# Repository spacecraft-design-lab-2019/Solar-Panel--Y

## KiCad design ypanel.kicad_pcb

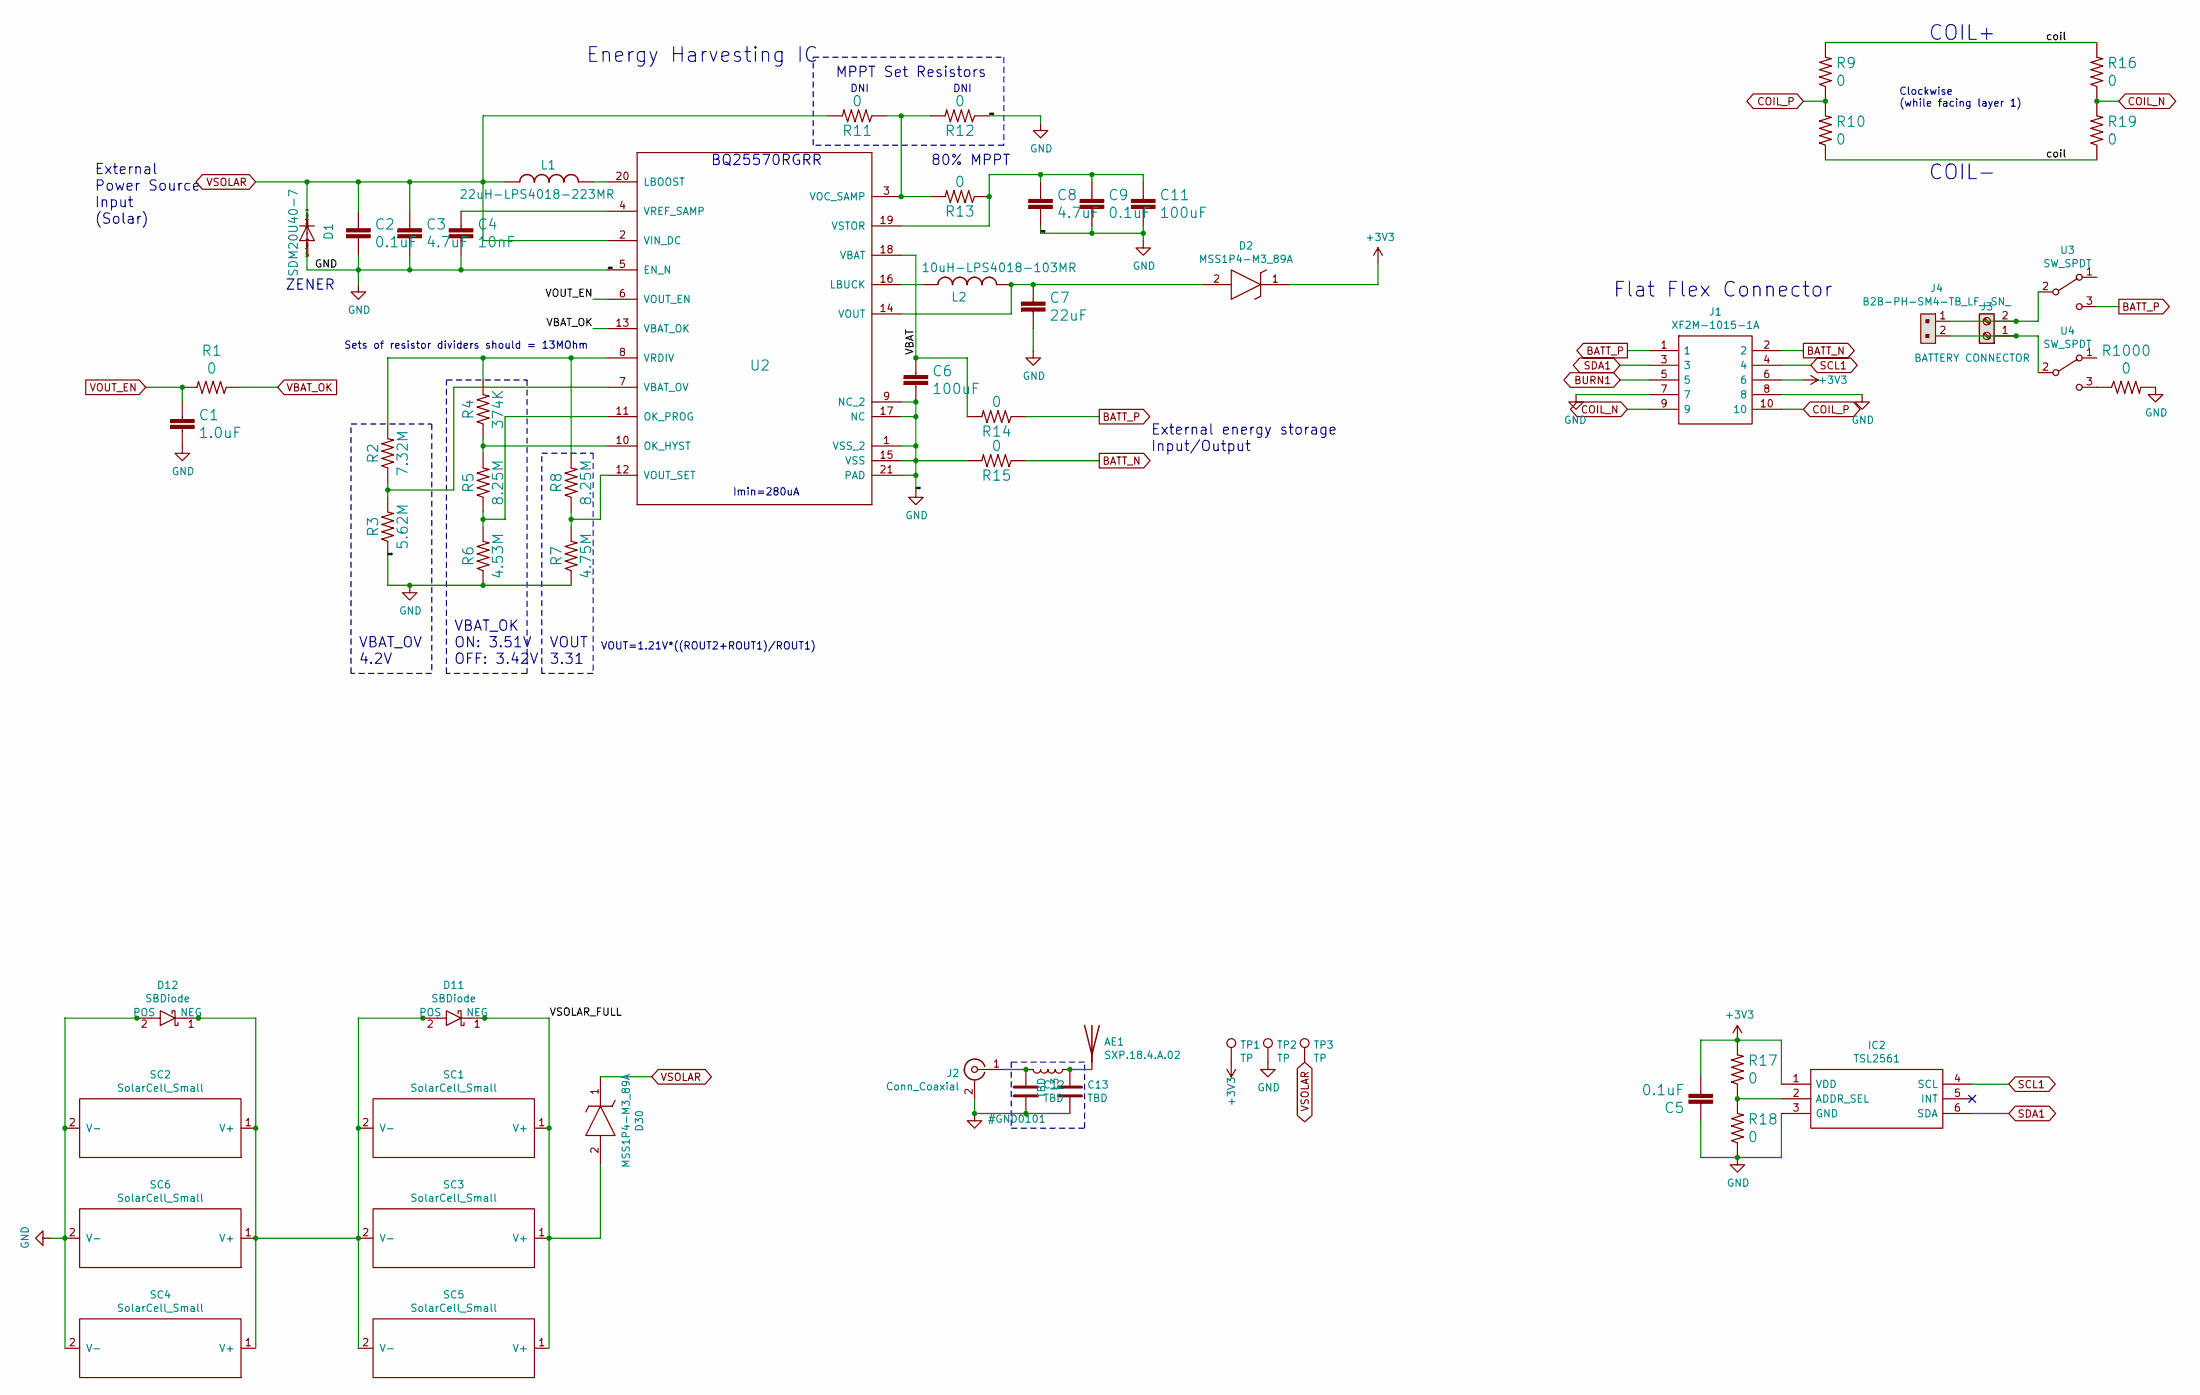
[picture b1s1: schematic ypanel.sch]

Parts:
AE1: SXP.18.4.A.02
C1: 1.0uF; C_0402_1005Metric
C2, C5, C9: 0.1uF; C_0402_1005Metric
C3, C8: 4.7uF; C_0402_1005Metric
C4: 10nF; C_0402_1005Metric
C6, C11: 100uF; C_0603_1608Metric
C7: 22uF; C_0402_1005Metric
C12, C13: TBD; C_0201_0603Metric
D1: SDM20U40-7; SOD523
D2, D30: MSS1P4-M3_89A; MICROSMP; Manufacturer_Part_Number MSS1P4-M3/89A; Mouser Part Number 625-MSS1P4-M3
D11, D12: SBDiode; SB Diode
IC2: TSL2561; Manufacturer_Part_Number TSL2561; Mouser Part Number N/A
J1: XF2M-1015-1A; Manufacturer_Part_Number XF2M-1015-1A; Mouser Part Number 653-XF2M-1015-1A
J2: Conn_Coaxial; U.FL_Hirose_U.FL-R-SMT-1_Vertical
J3: BATTERY CONNECTOR; SCREWTERMINAL-3.5MM-2_LOCK
J4: B2B-PH-SM4-TB_LF__SN_; JST_PH_B2B-PH-SM4-TB_1x02-1MP_P2.00mm_Vertical; MPN B2B-PH-SM4-TB(LF)(SN); Digi-Key_PN 455-1734-1-ND
L1: 22uH-LPS4018-223MR; LPS4018
L2: 10uH-LPS4018-103MR; LPS4018
L3: TBD; L_0201_0603Metric
R1, R9, R10, R11, R12, R13, R14, R15, R16, R17, R18, R19, R1000: 0; R_0402_1005Metric
R2: 7.32M; R_0402_1005Metric
R3: 5.62M; R_0402_1005Metric
R4: 374K; R_0402_1005Metric
R5, R8: 8.25M; R_0402_1005Metric
R6: 4.53M; R_0402_1005Metric
R7: 4.75M; R_0402_1005Metric
SC1, SC2, SC3, SC4, SC5, SC6: SolarCell_Small; KXOB25-05X3F
TP1, TP2, TP3: TP; TestPoint_THTPad_D1.0mm_Drill0.5mm
U2: Value; QFN50P350X350X100-21N-D
U3: SW_SPDT; D2F-L2-2
U4: SW_SPDT; D2F-L2

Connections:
+3V3: C5.2, D2.1, IC2.1 (VDD), J1.6, R17.2, TP1.1
/VBAT: C6.1, R14.2, U2.18 (VBAT)
/VSOLAR_FULL: D11.1 (NEG), D30.2, SC1.1 (V+), SC3.1 (V+), SC5.1 (V+)
/coil: R9.2, R10.1, R16.2, R19.1
BATT_N: J1.2, R15.1
BATT_P: J1.1, R14.1, U3.3 (C)
BURN1: J1.5
COIL_N: J1.9, R16.1, R19.2
COIL_P: J1.10, R9.1, R10.2
unnamed: AE1.1, C12.1, C13.1, J2.1 (In), L3.1, L3.2
unnamed: C4.1, U2.4 (VREF_SAMP)
unnamed: C7.1, D2.2, L2.2, U2.14 (VOUT)
unnamed: C8.1, C9.1, C11.1, R13.1, U2.19 (VSTOR)
unnamed: D11.2 (POS), D12.1 (NEG), SC1.2 (V-), SC2.1 (V+), SC3.2 (V-), SC4.1 (V+), SC5.2 (V-), SC6.1 (V+)
unnamed: IC2.2 (ADDR_SEL), R17.1, R18.2
unnamed: J3.1, J4.2, U4.2 (B)
unnamed: J3.2, J4.1, U3.2 (B)
unnamed: L1.2, U2.20 (LBOOST)
unnamed: L2.1, U2.16 (LBUCK)
unnamed: R2.1, R3.2, U2.7 (VBAT_OV)
unnamed: R2.2, R4.2, R8.2, U2.8 (VRDIV)
unnamed: R4.1, R5.2, U2.10 (OK_HYST)
unnamed: R5.1, R6.2, U2.11 (OK_PROG)
unnamed: R7.2, R8.1, U2.12 (VOUT_SET)
unnamed: R11.1, R12.2, R13.2, U2.3 (VOC_SAMP)
unnamed: R1000.1, U4.3 (C)
SCL1: IC2.4 (SCL), J1.4
SDA1: IC2.6 (SDA), J1.3
VBAT_OK: R1.1, U2.13 (VBAT_OK)
VOUT_EN: C1.1, R1.2, U2.6 (VOUT_EN)
VSOLAR: C2.1, C3.1, D1.C, D30.1, L1.1, R11.2, TP3.1, U2.2 (VIN_DC)

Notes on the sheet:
Flat Flex Connector
DNI
ZENER
VOUT 3.31
80% MPPT
VBAT_OK ON: 3.51V OFF: 3.42V
Imin=280uA
External Power Source Input (Solar)
External energy storage Input/Output
BQ25570RGRR
Energy Harvesting IC
VBAT_OV 4.2V
Sets of resistor dividers should = 13MOhm
VOUT=1.21V*((ROUT2+ROUT1)/ROUT1)
MPPT Set Resistors
COIL+
COIL-
Clockwise (while facing layer 1)

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
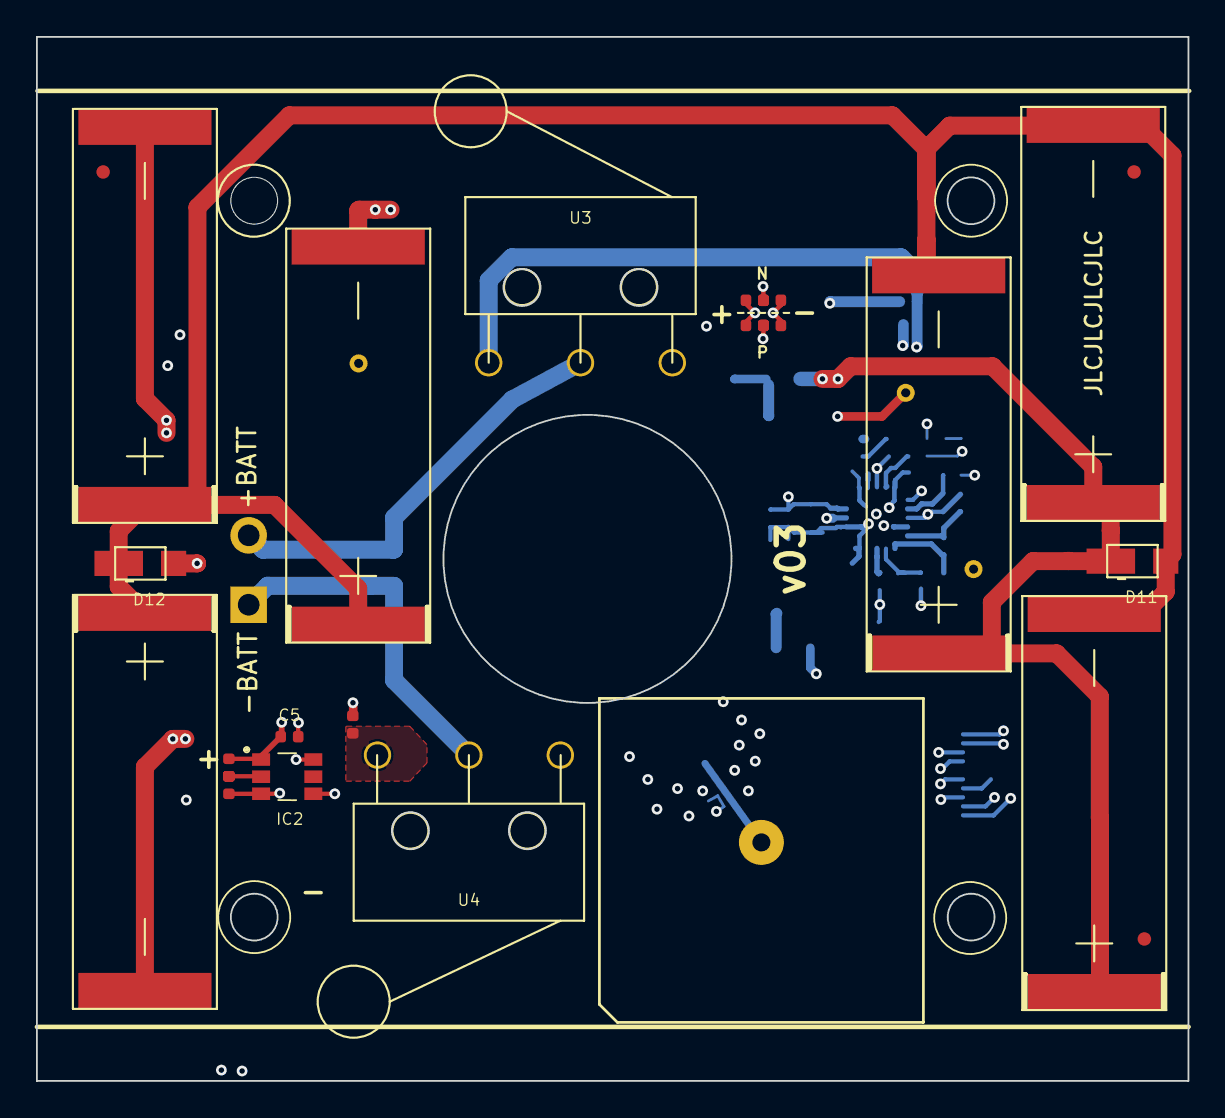
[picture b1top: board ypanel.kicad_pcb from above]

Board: 6 copper layers, 64.0 x 58.0 mm, 55 parts (0 on the bottom side), 31 nets.

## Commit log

2019-10-21 Added -Y PCB files (still in progress)
2019-10-23 Updated -Y PCB design
2019-10-24 Incorporated patch antenna and switches
2019-10-24 Added flatflex and phototransistor to -Y
2019-10-25 Added finished version 1 of -Y PCB
2019-10-25 starting on -Y board
2019-10-25 killer coils
2019-10-26 -Y board finished
2019-10-26 zipped fabrication files for all but +Y
2019-10-26 JLCPCB fab output
2019-10-26 adding interactive BOMs for +/-X,-Y,+-Z
2019-10-27 +Y panel read for fab
2019-10-27 JLCPCB output files
2019-10-29 Added step file of -Y panel
2019-10-30 Updated step file with additional 3D part models
2019-10-31 Added killswitches to step file
2019-11-01 stencil outputs
2019-11-14 Changed board outline to account for structures requirements
2019-12-03 Updated -Y PCB Layout
2019-12-03 Modified -Y Layout
2019-12-20 v01 order + repo overhaul
2020-02-12 repaired schematic so it matches PCB
2020-02-12 Updated -Y
    moved killswitches & flat-flex connector to new locations
2020-02-13 Added step file of -Y
2020-02-15 Added new antenna to -Y
2020-02-20 updated 3d footprint paths and generated new step file
2020-02-23 fixed antenna footprint and regenerated step file
2020-02-26 moved camera hole and other components
2020-02-28 Changed magnetorquer coils
2020-02-29 design review and gerber generation
2020-03-01 added fiducials, regenerated 3d model and gerbers
2020-08-29 clean up & manufacturing output for v2
2020-08-29 clean up & manufacturing output for v3
2020-08-29 should actually be v3
2020-08-30 fixing coil-to-board-edge distance...
2020-08-30 -y panel coils fixed and manufacturing files generated
2020-08-30 v3 out for order
